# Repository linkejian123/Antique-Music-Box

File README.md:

# Antique-Music-Box

### Description
-This project was originally a senior design project in Purdue University ECE477. 
-This is a music player capable of playing mp3 on SD card or stream Bluetooth music from Android devices. The music box has digital amplifier and valve tube pre-amp. The display used 60s style VFD tube from Soviet era.
-The Microcontroller used is Microchips dsPIC33FJ256GP710A.
- !!!!  Demo Vidoe here:https://www.youtube.com/watch?v=YaUscYTW8Vs&t=1s

### Authors
-Kejian Lin
-Ran An
-Yixing Liu
-Zhiyi Xiang

### Repository Structure

-`main`,`mp3`,`sd`, `AntiqueMB.X` are the code for the PIC microcontroller for main, mp3 and sd card as it states.
- `multithread` is the experimental multithread code.
- `arduino` is the interface code for Arduino Uno.
- `CAD` is the conceptual SolidWorks model for the project.
- `OBJ477` is the PCB files in Eagle. 

### Warning
 #### High voltage
 #### Some hotfix are not documented, yet

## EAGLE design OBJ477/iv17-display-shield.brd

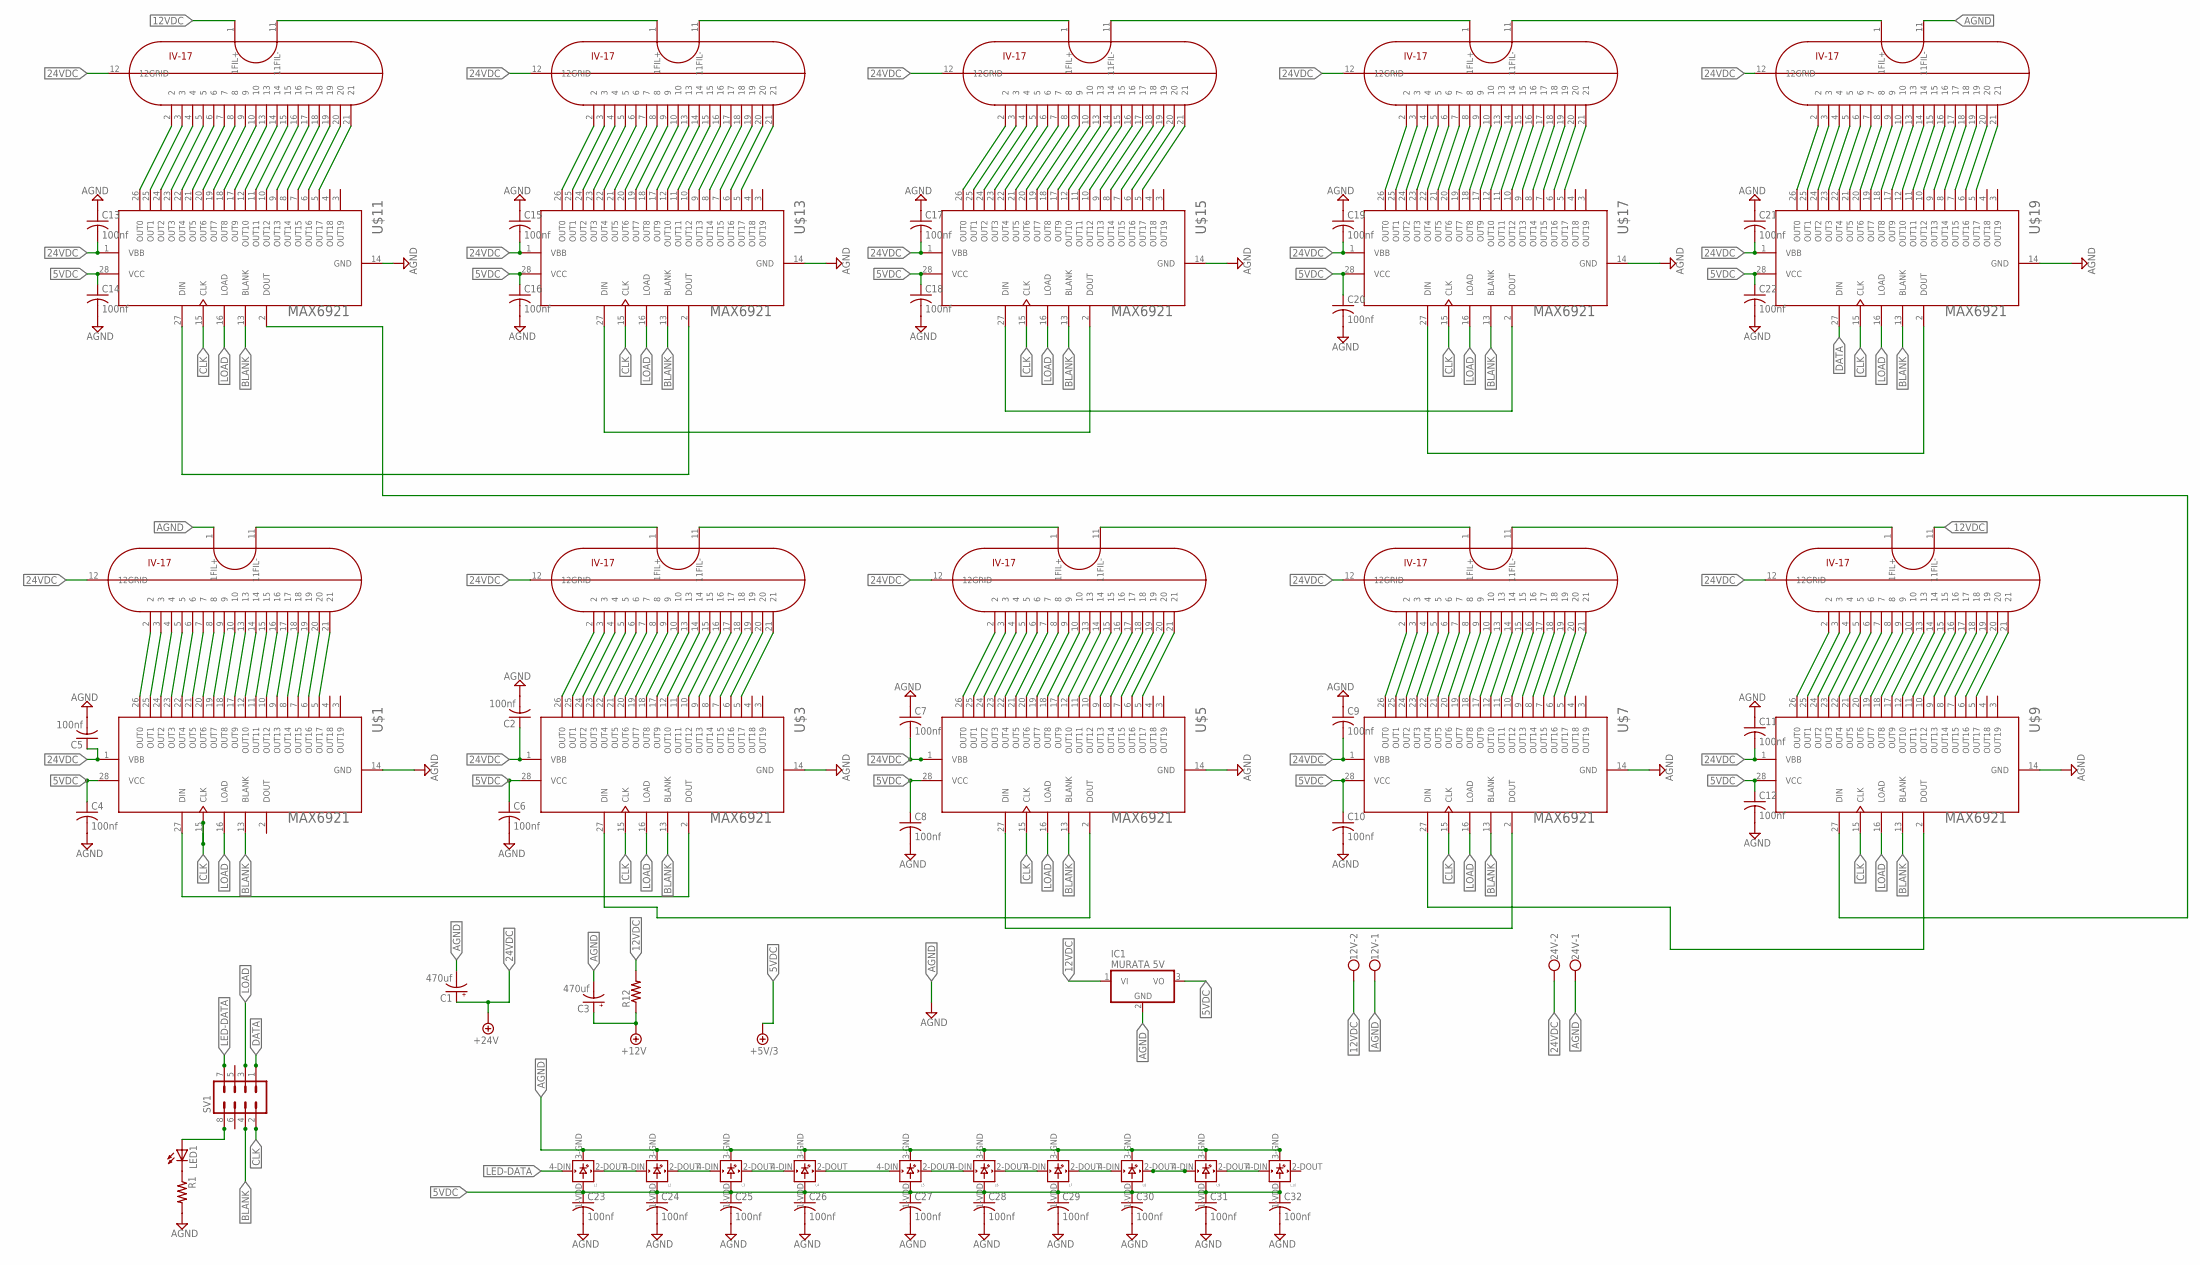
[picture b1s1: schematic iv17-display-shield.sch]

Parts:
12V, 24V: W237-102
C1, C3: 470uf; E5-10,5
C2, C4, C5, C6, C7, C8, C9, C10, C11, C12, C13, C14, C15, C16, C17, C18, C19, C20, C21, C22, C23, C24, C25, C26, C27, C28, C29, C30, C31, C32: 100nf; C1206
IC1: MURATA 5V; TO220V
L1, L2, L3, L4, L5, L6, L7, L8, L9, L10: WS2812B
LED1: LEDSMT1206; 1206
R1: R-US_R1206; R1206
R12: R-US_0207/10; 0207/10
SV1: MA04-2
U$1, U$3, U$5, U$7, U$9, U$11, U$13, U$15, U$17, U$19: MAX6921; SOIC-28W
U$2, U$4, U$6, U$8, U$10, U$12, U$14, U$16, U$18, U$20: IV17; NIXIE-22

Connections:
5VDC: C4.1, C6.1, C8.1, C10.1, C12.1, C14.1, C16.1, C18.1, C20.1, C22.1, C23.1, C24.1, C25.1, C26.1, C27.1, C28.1, C29.1, C30.1, C31.1, C32.1, IC1.3 (VO), L1.1-VDD (VDD), L2.1-VDD (VDD), L3.1-VDD (VDD), L4.1-VDD (VDD), L5.1-VDD (VDD), L6.1-VDD (VDD), L7.1-VDD (VDD), L8.1-VDD (VDD), L9.1-VDD (VDD), L10.1-VDD (VDD), U$1.28 (VCC), U$3.28 (VCC), U$5.28 (VCC), U$7.28 (VCC), U$9.28 (VCC), U$11.28 (VCC), U$13.28 (VCC), U$15.28 (VCC), U$17.28 (VCC), U$19.28 (VCC)
12VDC: 12V.2, IC1.1 (VI), R12.2, U$10.11 (11FIL-), U$12.1 (1FIL+)
24VDC: 24V.2, C1.+, C2.1, C5.1, C7.2, C9.2, C11.2, C13.2, C15.2, C17.2, C19.2, C21.2, U$1.1 (VBB), U$2.12 (12GRID), U$3.1 (VBB), U$4.12 (12GRID), U$5.1 (VBB), U$6.12 (12GRID), U$7.1 (VBB), U$8.12 (12GRID), U$9.1 (VBB), U$10.12 (12GRID), U$11.1 (VBB), U$12.12 (12GRID), U$13.1 (VBB), U$14.12 (12GRID), U$15.1 (VBB), U$16.12 (12GRID), U$17.1 (VBB), U$18.12 (12GRID), U$19.1 (VBB), U$20.12 (12GRID)
+12V: C3.+, R12.1
AGND: 12V.1, 24V.1, C1.-, C2.2, C3.-, C4.2, C5.2, C6.2, C7.1, C8.2, C9.1, C10.2, C11.1, C12.2, C13.1, C14.2, C15.1, C16.2, C17.1, C18.2, C19.1, C20.2, C21.1, C22.2, C23.2, C24.2, C25.2, C26.2, C27.2, C28.2, C29.2, C30.2, C31.2, C32.2, IC1.2 (GND), L1.3-GND (GND), L2.3-GND (GND), L3.3-GND (GND), L4.3-GND (GND), L5.3-GND (GND), L6.3-GND (GND), L7.3-GND (GND), L8.3-GND (GND), L9.3-GND (GND), L10.3-GND (GND), R1.2, U$1.14 (GND), U$2.1 (1FIL+), U$3.14 (GND), U$5.14 (GND), U$7.14 (GND), U$9.14 (GND), U$11.14 (GND), U$13.14 (GND), U$15.14 (GND), U$17.14 (GND), U$19.14 (GND), U$20.11 (11FIL-)
BLANK: SV1.4, U$1.13 (BLANK), U$3.13 (BLANK), U$5.13 (BLANK), U$7.13 (BLANK), U$9.13 (BLANK), U$11.13 (BLANK), U$13.13 (BLANK), U$15.13 (BLANK), U$17.13 (BLANK), U$19.13 (BLANK)
CLK: SV1.2, U$1.15 (CLK), U$3.15 (CLK), U$5.15 (CLK), U$7.15 (CLK), U$9.15 (CLK), U$11.15 (CLK), U$13.15 (CLK), U$15.15 (CLK), U$17.15 (CLK), U$19.15 (CLK)
DATA: SV1.1, U$19.27 (DIN)
LED-DATA: L1.4-DIN (DIN), SV1.7
LOAD: SV1.3, U$1.16 (LOAD), U$3.16 (LOAD), U$5.16 (LOAD), U$7.16 (LOAD), U$9.16 (LOAD), U$11.16 (LOAD), U$13.16 (LOAD), U$15.16 (LOAD), U$17.16 (LOAD), U$19.16 (LOAD)
unnamed: U$1.26 (OUT0), U$2.2
unnamed: U$1.25 (OUT1), U$2.3
unnamed: U$1.24 (OUT2), U$2.4
unnamed: U$1.23 (OUT3), U$2.5
unnamed: U$1.22 (OUT4), U$2.6
unnamed: U$1.21 (OUT5), U$2.7
unnamed: U$1.20 (OUT6), U$2.8
unnamed: U$1.19 (OUT7), U$2.9
unnamed: U$1.18 (OUT8), U$2.10
unnamed: U$1.17 (OUT9), U$2.13
unnamed: U$1.12 (OUT10), U$2.14
unnamed: U$1.11 (OUT11), U$2.15
unnamed: U$1.10 (OUT12), U$2.16
unnamed: U$1.9 (OUT13), U$2.17
unnamed: U$1.8 (OUT14), U$2.18
unnamed: U$1.7 (OUT15), U$2.19
unnamed: U$1.6 (OUT16), U$2.20
unnamed: U$1.5 (OUT17), U$2.21
unnamed: U$3.26 (OUT0), U$4.2
unnamed: U$3.25 (OUT1), U$4.3
unnamed: U$3.24 (OUT2), U$4.4
unnamed: U$3.23 (OUT3), U$4.5
unnamed: U$17.27 (DIN), U$19.2 (DOUT)
unnamed: U$3.22 (OUT4), U$4.6
unnamed: U$3.21 (OUT5), U$4.7
unnamed: U$3.20 (OUT6), U$4.8
unnamed: U$3.19 (OUT7), U$4.9
unnamed: U$3.18 (OUT8), U$4.10
unnamed: U$3.17 (OUT9), U$4.13
unnamed: U$3.12 (OUT10), U$4.14
unnamed: U$3.11 (OUT11), U$4.15
unnamed: U$3.10 (OUT12), U$4.16
unnamed: U$3.9 (OUT13), U$4.17
unnamed: U$3.8 (OUT14), U$4.18
unnamed: U$3.7 (OUT15), U$4.19
unnamed: U$3.6 (OUT16), U$4.20
unnamed: U$3.5 (OUT17), U$4.21
unnamed: U$5.26 (OUT0), U$6.2
unnamed: U$5.25 (OUT1), U$6.3
unnamed: U$5.24 (OUT2), U$6.4
unnamed: U$15.27 (DIN), U$17.2 (DOUT)
unnamed: U$5.23 (OUT3), U$6.5
unnamed: U$5.22 (OUT4), U$6.6
unnamed: U$5.21 (OUT5), U$6.7
unnamed: U$5.20 (OUT6), U$6.8
unnamed: U$5.19 (OUT7), U$6.9
unnamed: U$5.18 (OUT8), U$6.10
unnamed: U$5.17 (OUT9), U$6.13
unnamed: U$5.12 (OUT10), U$6.14
unnamed: U$5.11 (OUT11), U$6.15
unnamed: U$5.10 (OUT12), U$6.16
unnamed: U$5.9 (OUT13), U$6.17
unnamed: U$5.8 (OUT14), U$6.18
unnamed: U$5.7 (OUT15), U$6.19
unnamed: U$5.6 (OUT16), U$6.20
unnamed: U$5.5 (OUT17), U$6.21
unnamed: U$7.26 (OUT0), U$8.2
unnamed: U$7.25 (OUT1), U$8.3
unnamed: U$7.24 (OUT2), U$8.4
unnamed: U$7.23 (OUT3), U$8.5
unnamed: U$7.22 (OUT4), U$8.6
unnamed: U$7.21 (OUT5), U$8.7
unnamed: U$11.27 (DIN), U$13.2 (DOUT)
unnamed: U$7.20 (OUT6), U$8.8
unnamed: U$7.19 (OUT7), U$8.9
unnamed: U$7.18 (OUT8), U$8.10
unnamed: U$7.17 (OUT9), U$8.13
unnamed: U$7.12 (OUT10), U$8.14
unnamed: U$7.11 (OUT11), U$8.15
unnamed: U$7.10 (OUT12), U$8.16
unnamed: U$7.9 (OUT13), U$8.17
unnamed: U$7.8 (OUT14), U$8.18
unnamed: U$7.7 (OUT15), U$8.19
unnamed: U$7.6 (OUT16), U$8.20
unnamed: U$7.5 (OUT17), U$8.21
unnamed: U$9.26 (OUT0), U$10.2
unnamed: U$9.25 (OUT1), U$10.3
unnamed: U$9.24 (OUT2), U$10.4
unnamed: U$9.23 (OUT3), U$10.5
unnamed: U$9.22 (OUT4), U$10.6
unnamed: U$9.21 (OUT5), U$10.7
unnamed: U$9.20 (OUT6), U$10.8
unnamed: U$9.19 (OUT7), U$10.9
unnamed: U$9.18 (OUT8), U$10.10
unnamed: U$9.27 (DIN), U$11.2 (DOUT)
unnamed: U$9.17 (OUT9), U$10.13
unnamed: U$9.12 (OUT10), U$10.14
unnamed: U$9.11 (OUT11), U$10.15
unnamed: U$9.10 (OUT12), U$10.16
unnamed: U$9.9 (OUT13), U$10.17
unnamed: U$9.8 (OUT14), U$10.18
unnamed: U$9.7 (OUT15), U$10.19
unnamed: U$9.6 (OUT16), U$10.20
unnamed: U$9.5 (OUT17), U$10.21
unnamed: U$11.26 (OUT0), U$12.2
unnamed: U$11.25 (OUT1), U$12.3
unnamed: U$11.24 (OUT2), U$12.4
unnamed: U$11.23 (OUT3), U$12.5
unnamed: U$11.22 (OUT4), U$12.6
unnamed: U$11.21 (OUT5), U$12.7
unnamed: U$11.20 (OUT6), U$12.8
unnamed: U$11.19 (OUT7), U$12.9
unnamed: U$11.18 (OUT8), U$12.10
unnamed: U$11.17 (OUT9), U$12.13
unnamed: U$11.12 (OUT10), U$12.14
unnamed: U$11.11 (OUT11), U$12.15
unnamed: U$7.27 (DIN), U$9.2 (DOUT)
unnamed: U$11.10 (OUT12), U$12.16
unnamed: L1.2-DOUT (DOUT), L2.4-DIN (DIN)
unnamed: L2.2-DOUT (DOUT), L3.4-DIN (DIN)
unnamed: U$8.11 (11FIL-), U$10.1 (1FIL+)
unnamed: U$6.11 (11FIL-), U$8.1 (1FIL+)
unnamed: U$4.11 (11FIL-), U$6.1 (1FIL+)
unnamed: U$2.11 (11FIL-), U$4.1 (1FIL+)
unnamed: U$11.9 (OUT13), U$12.17
unnamed: U$11.8 (OUT14), U$12.18
unnamed: U$11.7 (OUT15), U$12.19
unnamed: U$11.6 (OUT16), U$12.20
unnamed: U$11.5 (OUT17), U$12.21
unnamed: U$13.26 (OUT0), U$14.2
unnamed: U$13.25 (OUT1), U$14.3
unnamed: U$13.24 (OUT2), U$14.4
unnamed: U$13.23 (OUT3), U$14.5
unnamed: U$13.22 (OUT4), U$14.6
unnamed: U$13.21 (OUT5), U$14.7
unnamed: U$13.20 (OUT6), U$14.8
unnamed: U$13.19 (OUT7), U$14.9
unnamed: U$13.18 (OUT8), U$14.10
unnamed: U$13.17 (OUT9), U$14.13
unnamed: U$13.12 (OUT10), U$14.14
unnamed: U$13.11 (OUT11), U$14.15
unnamed: U$13.10 (OUT12), U$14.16
unnamed: U$5.27 (DIN), U$7.2 (DOUT)
unnamed: U$13.9 (OUT13), U$14.17
unnamed: L3.2-DOUT (DOUT), L4.4-DIN (DIN)
unnamed: U$13.8 (OUT14), U$14.18
unnamed: U$13.7 (OUT15), U$14.19
unnamed: U$13.6 (OUT16), U$14.20
unnamed: U$13.5 (OUT17), U$14.21
unnamed: U$15.26 (OUT0), U$16.2
unnamed: U$15.25 (OUT1), U$16.3
unnamed: U$15.24 (OUT2), U$16.4
unnamed: U$15.23 (OUT3), U$16.5
unnamed: U$15.22 (OUT4), U$16.6
unnamed: U$15.21 (OUT5), U$16.7
unnamed: U$15.20 (OUT6), U$16.8
unnamed: U$15.19 (OUT7), U$16.9
unnamed: U$15.18 (OUT8), U$16.10
unnamed: U$15.17 (OUT9), U$16.13
unnamed: U$15.12 (OUT10), U$16.14
unnamed: U$15.11 (OUT11), U$16.15
unnamed: U$15.10 (OUT12), U$16.16
unnamed: U$15.9 (OUT13), U$16.17
unnamed: U$15.8 (OUT14), U$16.18
unnamed: U$3.27 (DIN), U$5.2 (DOUT)
unnamed: U$15.7 (OUT15), U$16.19
unnamed: L4.2-DOUT (DOUT), L5.4-DIN (DIN)
unnamed: L5.2-DOUT (DOUT), L6.4-DIN (DIN)
unnamed: U$15.6 (OUT16), U$16.20
unnamed: U$15.5 (OUT17), U$16.21
unnamed: U$17.26 (OUT0), U$18.2
unnamed: U$17.25 (OUT1), U$18.3
unnamed: U$17.24 (OUT2), U$18.4
unnamed: U$17.23 (OUT3), U$18.5
unnamed: U$17.22 (OUT4), U$18.6
unnamed: U$17.21 (OUT5), U$18.7
unnamed: U$17.20 (OUT6), U$18.8
unnamed: U$17.19 (OUT7), U$18.9
unnamed: U$17.18 (OUT8), U$18.10
unnamed: U$17.17 (OUT9), U$18.13
unnamed: U$17.12 (OUT10), U$18.14
unnamed: U$17.11 (OUT11), U$18.15
unnamed: U$17.10 (OUT12), U$18.16
unnamed: U$17.9 (OUT13), U$18.17
unnamed: U$17.8 (OUT14), U$18.18
unnamed: U$17.7 (OUT15), U$18.19
unnamed: U$13.27 (DIN), U$15.2 (DOUT)
unnamed: U$17.6 (OUT16), U$18.20
unnamed: L6.2-DOUT (DOUT), L7.4-DIN (DIN)
unnamed: L7.2-DOUT (DOUT), L8.4-DIN (DIN)
unnamed: U$17.5 (OUT17), U$18.21
unnamed: U$19.26 (OUT0), U$20.2
unnamed: U$19.25 (OUT1), U$20.3
unnamed: U$19.24 (OUT2), U$20.4
unnamed: U$19.23 (OUT3), U$20.5
unnamed: U$19.22 (OUT4), U$20.6
unnamed: U$19.21 (OUT5), U$20.7
unnamed: U$19.20 (OUT6), U$20.8
unnamed: U$19.19 (OUT7), U$20.9
unnamed: U$19.18 (OUT8), U$20.10
unnamed: U$19.17 (OUT9), U$20.13
unnamed: U$19.12 (OUT10), U$20.14
unnamed: U$19.11 (OUT11), U$20.15
unnamed: U$19.10 (OUT12), U$20.16
unnamed: U$19.9 (OUT13), U$20.17
unnamed: U$19.8 (OUT14), U$20.18
unnamed: U$19.7 (OUT15), U$20.19
unnamed: U$19.6 (OUT16), U$20.20
unnamed: U$1.27 (DIN), U$3.2 (DOUT)
unnamed: U$19.5 (OUT17), U$20.21
unnamed: L8.2-DOUT (DOUT), L9.4-DIN (DIN)
unnamed: L9.2-DOUT (DOUT), L10.4-DIN (DIN)
unnamed: LED1.C, R1.1
unnamed: LED1.A, SV1.8
unnamed: U$18.11 (11FIL-), U$20.1 (1FIL+)
unnamed: U$16.11 (11FIL-), U$18.1 (1FIL+)
unnamed: U$14.11 (11FIL-), U$16.1 (1FIL+)
unnamed: U$12.11 (11FIL-), U$14.1 (1FIL+)

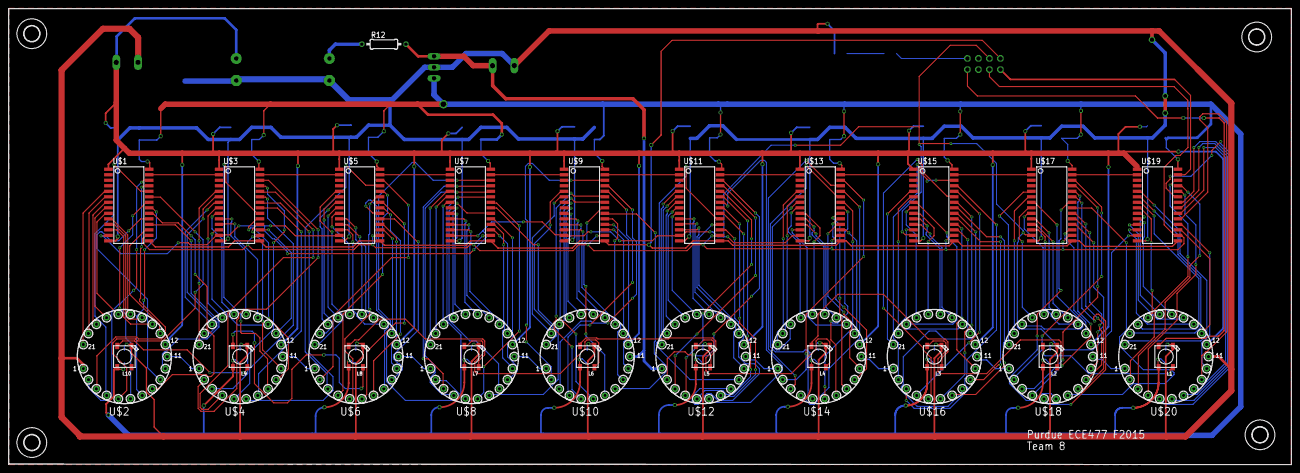
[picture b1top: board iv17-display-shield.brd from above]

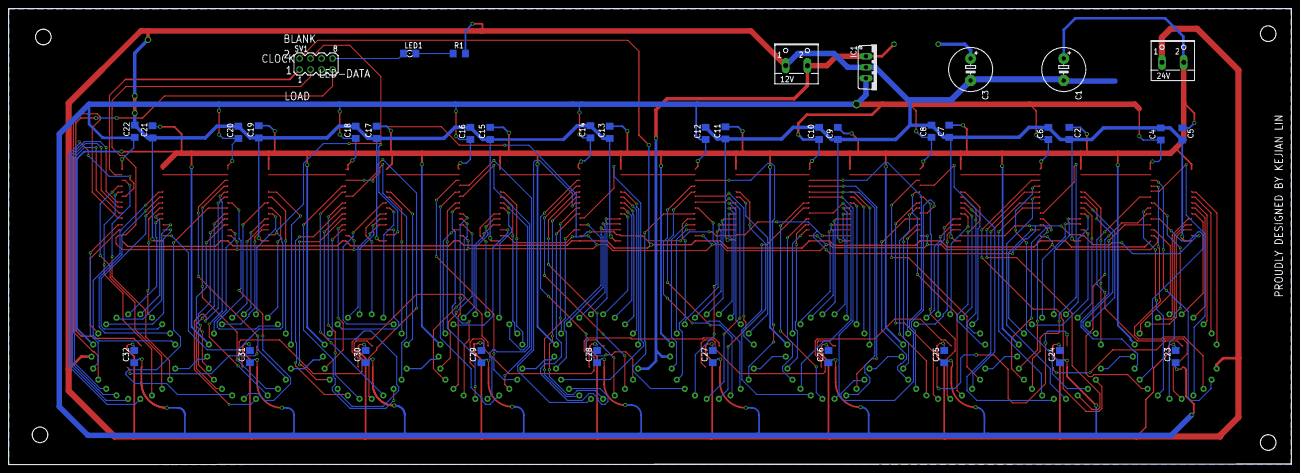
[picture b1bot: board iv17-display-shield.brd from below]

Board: 2 copper layers, 295.6 x 105.1 mm, 73 parts (38 on the bottom side), 218 nets.

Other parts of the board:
U$21, U$22, U$23, U$24: 3,6

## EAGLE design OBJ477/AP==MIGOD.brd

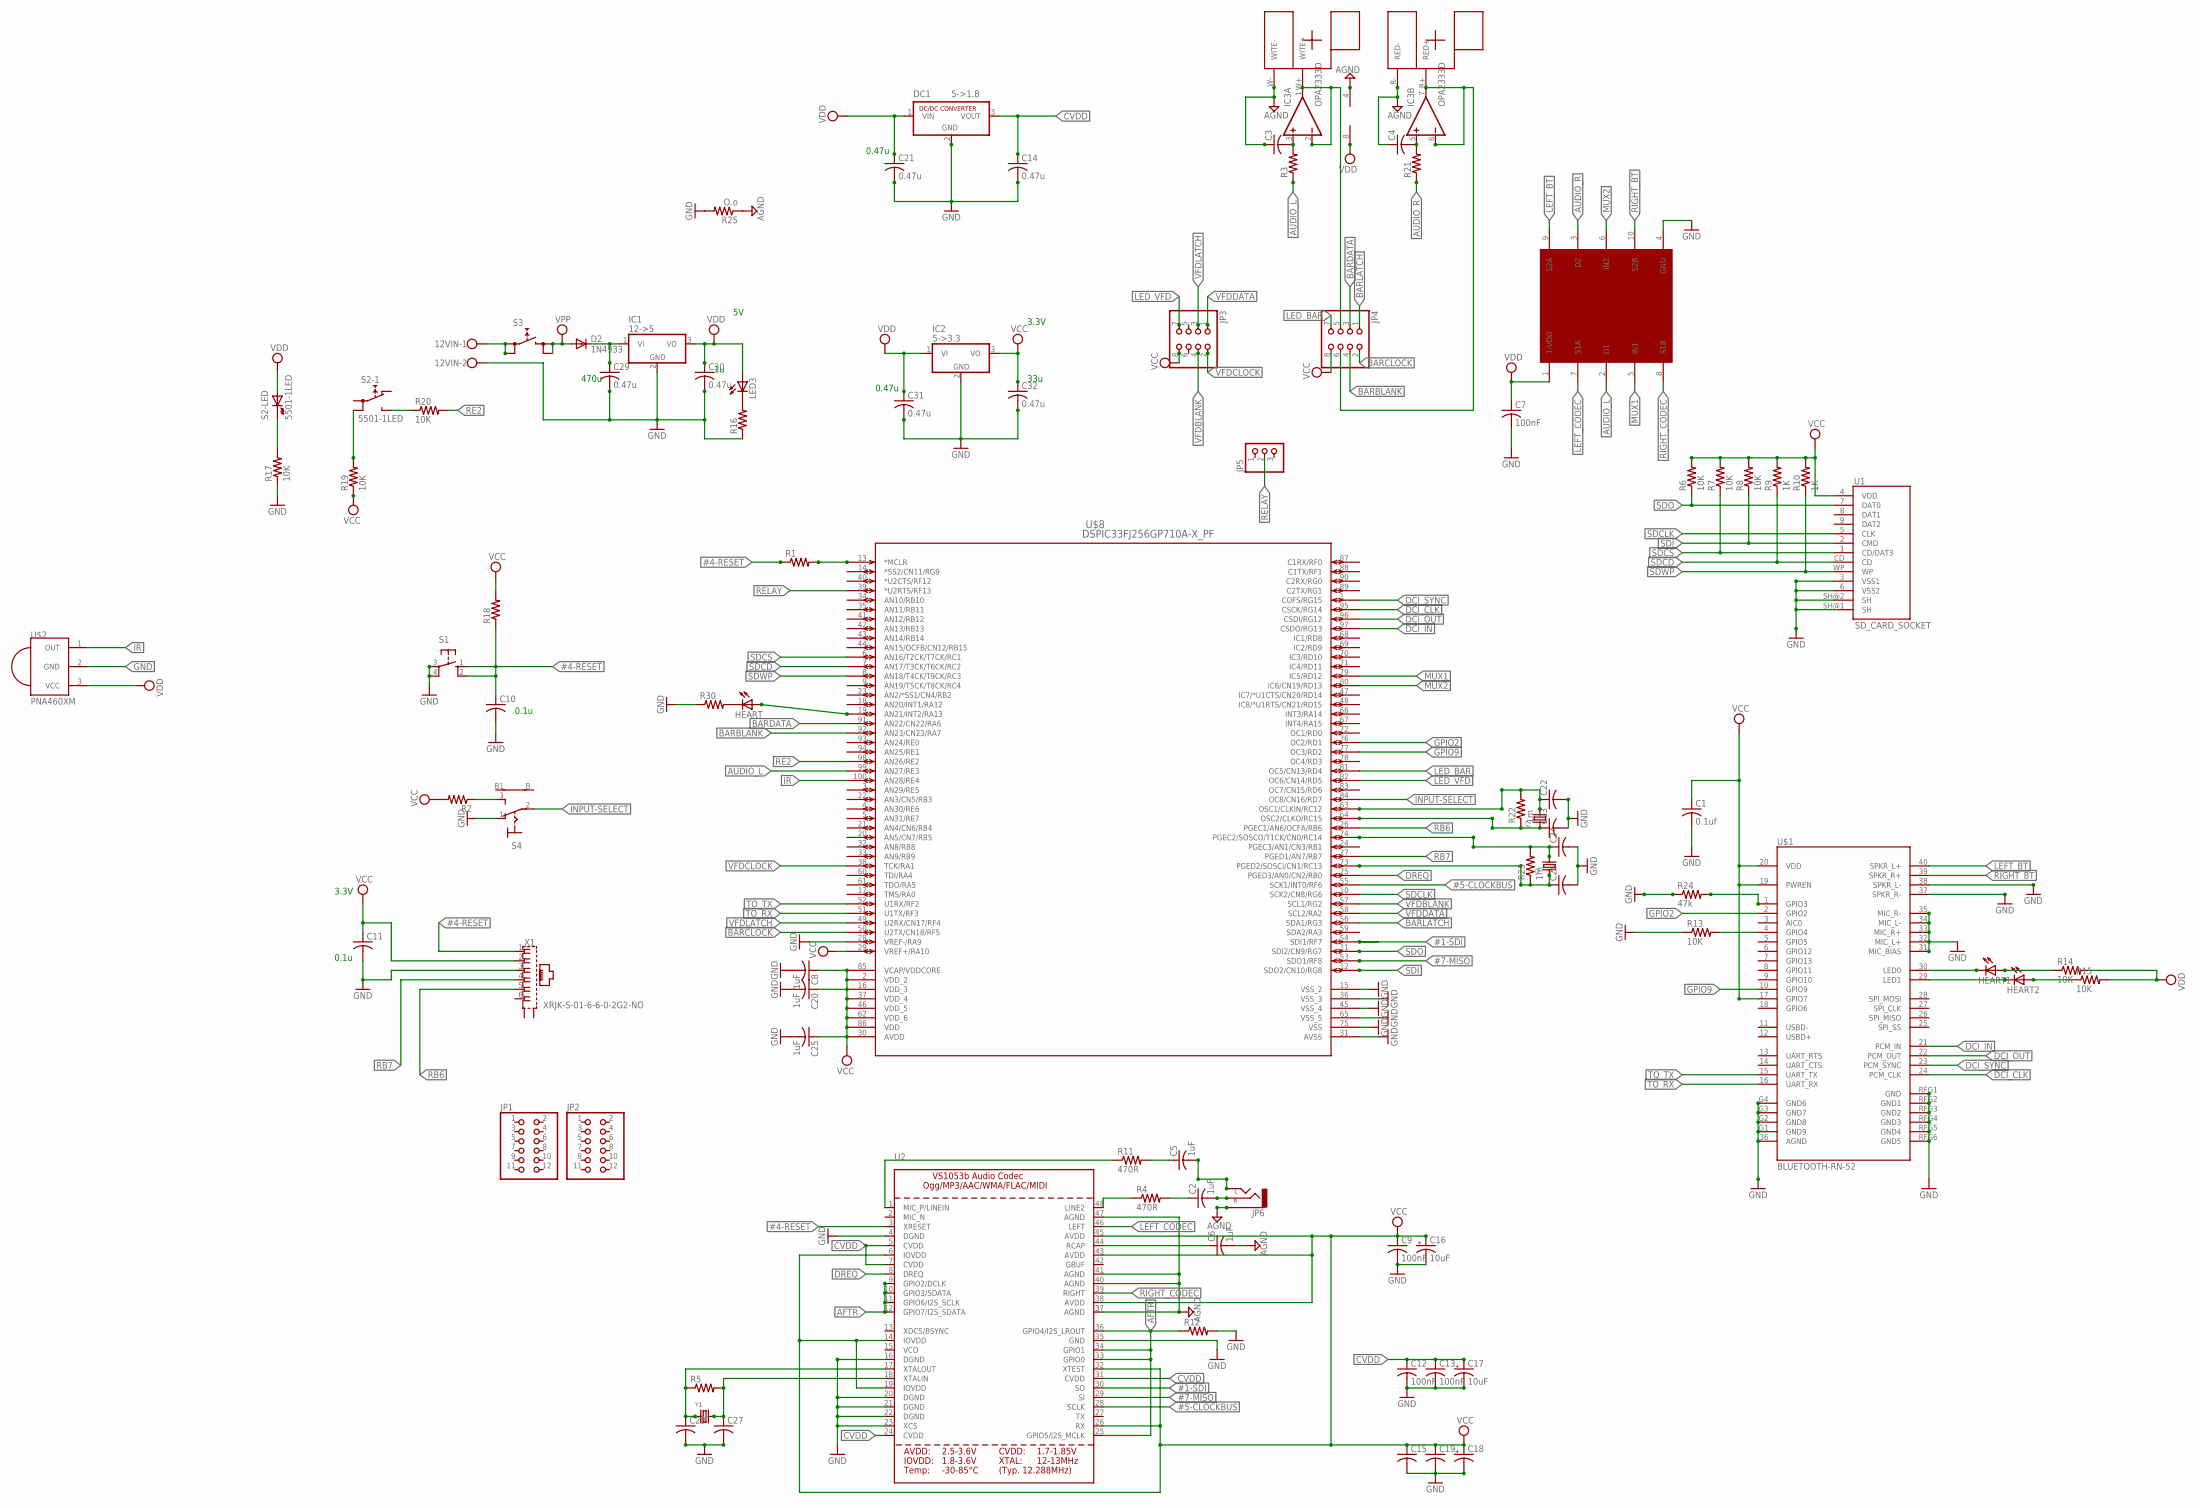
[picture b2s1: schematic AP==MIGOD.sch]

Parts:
12VIN: W237-102
C1: 0.1uf; C1206
C2, C5, C6, C8, C20, C25: 1uF; C1206
C3, C4: C-US050-030X075; C050-030X075
C7, C9, C12, C13: 100nF; C1206
C10, C11, C15, C19, C22, C23, C24, C26, C27, C28: C-USC1206; C1206
C14, C21, C29, C30, C31, C32: 0.47u; C1206
C16, C17: 10uF; E5-8,5
C18: CPOL-USE5-8.5; E5-8,5
D2: 1N4933; DO41-10
DC1: 5->1.8; SIP3
HEART, HEART1, HEART2: LEDSMT1206; 1206
IC1: 12->5; TO220V
IC2: 5->3.3; TO220V
IC3: OPA2333D; SO08
JP1, JP2: PINHD-2X6; 2X06
JP3, JP4: PINHD-2X4; 2X04
JP5: PINHD-1X3; 1X03
JP6: AUDIO-JACKPTH; AUDIO-JACK
LED3: LEDSMT1206; 1206
R1, R2, R5, R12, R16, R18, R30: R-US_R1206; R1206
R3, R21: R-US_0207/10; 0207/10
R4, R11: 470R; R1206
R6, R7, R8, R13, R14, R15, R17, R19, R20: 10K; R1206
R9, R10: 1K; R1206
R22, R23: 1m; R1206
R24: 47k; R1206
R25: O.o; R1206
S1: 10-XX; B3F-10XX
S2: 5501-1LED
S3: REKN
S4: 9070-1W
U1: SD_CARD_SOCKET; SD_1:1
U2: VS1053B; LQFP48
U$1: BLUETOOTH-RN-52; RN-52
U$2: PNA460XM
U$8: DSPIC33FJ256GP710A-X_PF; TQFP100_14X14MC
U$13: RCANEW; RCA
U$15: ADG884; MSOP10
X1: XRJK-S-01-6-6-0-2G2-NO
Y1, Y2, Y3: CRYSTALTHIN; CRYSTAL_3.2X2.5

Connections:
#1-SDI: U2.30 (SO), U$8.54 (SDI1/RF7)
#4-RESET: C10.1, R1.1, R18.1, S1.1 (S), S1.2 (S1), U2.3 (XRESET), X1.1
#5-CLOCKBUS: U2.28 (SCLK), U$8.55 (SCK1/INT0/RF6)
#7-MISO: U2.29 (SI), U$8.53 (SDO1/RF8)
AFTR: R12.1, U2.9 (GPIO2/DCLK), U2.10 (GPIO3/SDATA), U2.11 (GPIO6/I2S_SCLK), U2.12 (GPIO7/I2S_SDATA), U2.25 (GPIO5/I2S_MCLK), U2.33 (GPIO0), U2.34 (GPIO1), U2.36 (GPIO4/I2S_LROUT)
AGND: C3.1, C4.1, C6.2, IC3.4 (V-), JP6.SLEEVE, R25.1, U2.37 (AGND), U2.40 (AGND), U2.41 (AGND), U2.47 (AGND), U$13.R- (RED-), U$13.W- (WITE-)
AUDIO_L: R3.1, U$8.99 (AN27/RE3), U$15.2 (D1)
AUDIO_R: R21.1, U$15.3 (D2)
BARBLANK: JP4.4, U$8.92 (AN23/CN23/RA7)
BARCLOCK: JP4.2, U$8.50 (U2TX/CN18/RF5)
BARDATA: JP4.3, U$8.91 (AN22/CN22/RA6)
BARLATCH: JP4.1, U$8.56 (SDA1/RG3)
CVDD: C12.1, C13.1, C14.1, C17.+, DC1.3 (VOUT), U2.5 (CVDD), U2.7 (CVDD), U2.24 (CVDD), U2.31 (CVDD)
DCI_CLK: U$1.24 (PCM_CLK), U$8.95 (CSCK/RG14)
DCI_IN: U$1.21 (PCM_IN), U$8.97 (CSDO/RG13)
DCI_OUT: U$1.22 (PCM_OUT), U$8.96 (CSDI/RG12)
DCI_SYNC: U$1.23 (PCM_SYNC), U$8.1 (COFS/RG15)
DREQ: U2.8 (DREQ), U$8.25 (PGED3/AN0/CN2/RB0)
GND: 12VIN.2, C1.2, C7.2, C8.2, C9.2, C10.2, C11.2, C12.2, C13.2, C14.2, C15.2, C16.-, C17.-, C18.-, C19.2, C20.2, C21.2, C22.2, C23.2, C24.2, C25.2, C26.2, C27.2, C28.2, C29.2, C30.2, C31.2, C32.2, DC1.2 (GND), IC1.2 (GND), IC2.2 (GND), R12.2, R13.1, R16.1, R17.1, R24.1, R25.2, R30.1, S1.3, S1.4 (P1), S4.1 (O), U1.3 (VSS1), U1.6 (VSS2), U1.SH@1 (SH), U1.SH@2 (SH), U2.4 (DGND), U2.16 (DGND), U2.20 (DGND), U2.21 (DGND), U2.22 (DGND), U2.23 (XCS), U2.35 (GND), U$1.31 (MIC_BIAS), U$1.32 (MIC_L+), U$1.33 (MIC_R+), U$1.34 (MIC_L-), U$1.35 (MIC_R-), U$1.36 (AGND), U$1.37 (SPKR_R-), U$1.38 (SPKR_L-), U$1.G1 (GND9), U$1.G2 (GND8), U$1.G3 (GND7), U$1.G4 (GND6), U$1.RFG1 (GND), U$1.RFG2 (GND1), U$1.RFG3 (GND2), U$1.RFG4 (GND3), U$1.RFG5 (GND4), U$1.RFG6 (GND5), U$2.2 (GND), U$8.15 (VSS_2), U$8.28 (VREF-/RA9), U$8.31 (AVSS), U$8.36 (VSS_3), U$8.45 (VSS_4), U$8.65 (VSS_5), U$8.75 (VSS), U$15.4 (GND), X1.3
GPIO2: U$1.2 (GPIO2), U$8.76 (OC2/RD1)
GPIO9: U$1.10 (GPIO9), U$8.77 (OC3/RD2)
INPUT-SELECT: S4.2, U$8.84 (OC8/CN16/RD7)
IR: U$2.1 (OUT), U$8.100 (AN28/RE4)
LED_BAR: JP4.7, U$8.81 (OC5/CN13/RD4)
LED_VFD: JP3.7, U$8.82 (OC6/CN14/RD5)
LEFT_BT: U$1.40 (SPKR_L+), U$15.9 (S2A)
LEFT_CODEC: U2.46 (LEFT), U$15.7 (S1A)
MUX1: U$8.79 (IC5/RD12), U$15.5 (IN1)
MUX2: U$8.80 (IC6/CN19/RD13), U$15.6 (IN2)
unnamed: C2.2, JP6.RING (RIGHT)
unnamed: R1.2, U$8.13 (*MCLR)
unnamed: LED3.C, R16.2
unnamed: C6.1, U2.44 (RCAP)
unnamed: R19.2, S2.1B
unnamed: C28.1, R5.1, U2.17 (XTALOUT), Y1.1
unnamed: C27.1, R5.2, U2.18 (XTALIN), Y1.2
unnamed: C2.1, R4.2
unnamed: R4.1, U2.48 (LINE2)
unnamed: C5.2, JP6.TIP (LEFT)
unnamed: C5.1, R11.2
unnamed: R11.1, U2.1 (MIC_P/LINEIN)
unnamed: C24.1, R23.2, U$8.74 (PGEC2/SOSCO/T1CK/CN0/RC14), Y3.2
unnamed: R13.2, U$1.4 (GPIO4)
unnamed: C29.1, D2.C, IC1.1 (VI)
unnamed: HEART1.C, U$1.30 (LED0)
unnamed: HEART2.C, U$1.29 (LED1)
unnamed: HEART1.A, R14.1
unnamed: HEART2.A, R15.1
unnamed: C22.1, R22.2, U$8.63 (OSC1/CLKIN/RC12), Y2.2
unnamed: IC3.1 (OUT), IC3.2 (-IN), JP4.5, U$13.W+ (WITE+)
unnamed: IC3.6 (-IN), IC3.7 (OUT), JP4.6, U$13.R+ (RED+)
unnamed: C3.2, IC3.3 (+IN), R3.2
unnamed: R17.2, S2.- (K)
unnamed: R20.1, S2.NO
unnamed: 12VIN.1, S3.0A (0), S3.0B (0)
unnamed: C4.2, IC3.5 (+IN), R21.2
unnamed: R2.1, S4.3 (S)
unnamed: R24.2, U$1.1 (GPIO3)
unnamed: C23.1, R22.1, U$8.64 (OSC2/CLKO/RC15), Y2.1
unnamed: C26.1, R23.1, U$8.73 (PGED2/SOSCI/CN1/RC13), Y3.1
unnamed: HEART.A, U$8.19 (AN21/INT2/RA13)
unnamed: HEART.C, R30.2
RB6: U$8.26 (PGEC1/AN6/OCFA/RB6), X1.5
RB7: U$8.27 (PGED1/AN7/RB7), X1.4
RE2: R20.2, U$8.98 (AN26/RE2)
RELAY: JP5.2, U$8.39 (*U2RTS/RF13)
RIGHT_BT: U$1.39 (SPKR_R+), U$15.10 (S2B)
RIGHT_CODEC: U2.39 (RIGHT), U$15.8 (S1B)
SDCD: R9.1, U1.CD, U$8.7 (AN17/T3CK/T6CK/RC2)
SDCLK: U1.5 (CLK), U$8.10 (SCK2/CN8/RG6)
SDCS: R7.1, U1.1 (CD/DAT3), U$8.6 (AN16/T2CK/T7CK/RC1)
SDI: R8.1, U1.2 (CMD), U$8.12 (SDO2/CN10/RG8)
SDO: R6.1, U1.7 (DAT0), U$8.11 (SDI2/CN9/RG7)
SDWP: R10.1, U1.WP, U$8.8 (AN18/T4CK/T9CK/RC3)
TO_RX: U$1.16 (UART_RX), U$8.51 (U1TX/RF3)
TO_TX: U$1.15 (UART_TX), U$8.52 (U1RX/RF2)
VCC: C1.1, C8.1, C9.1, C11.1, C15.1, C16.+, C18.+, C19.1, C20.1, C25.1, C32.1, IC2.3 (VO), JP3.8, JP4.8, R2.2, R6.2, R7.2, R8.2, R9.2, R10.2, R18.2, R19.1, U1.4 (VDD), U2.6 (IOVDD), U2.14 (IOVDD), U2.19 (IOVDD), U2.26 (RX), U2.32 (XTEST), U2.38 (AVDD), U2.43 (AVDD), U2.45 (AVDD), U$1.17 (GPIO7), U$1.19 (PWREN), U$1.20 (VDD), U$8.2 (VDD_2), U$8.16 (VDD_3), U$8.29 (VREF+/RA10), U$8.30 (AVDD), U$8.37 (VDD_4), U$8.46 (VDD_5), U$8.62 (VDD_6), U$8.85 (VCAP/VDDCORE), U$8.86 (VDD), X1.2
VDD: C7.1, C21.1, C30.1, C31.1, DC1.1 (VIN), IC1.3 (VO), IC2.1 (VI), IC3.8 (V+), LED3.A, R14.2, R15.2, S2.+ (A), U$2.3 (VCC), U$15.1 (1-VDD)
VFDBLANK: JP3.4, U$8.57 (SCL1/RG2)
VFDCLOCK: JP3.2, U$8.38 (TCK/RA1)
VFDDATA: JP3.1, U$8.58 (SCL2/RA2)
VFDLATCH: JP3.3, U$8.49 (U2RX/CN17/RF4)
VPP: D2.A, S3.1A (1), S3.1B (1)

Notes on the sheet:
0.1u
3.3V
470u
0.47u
33u

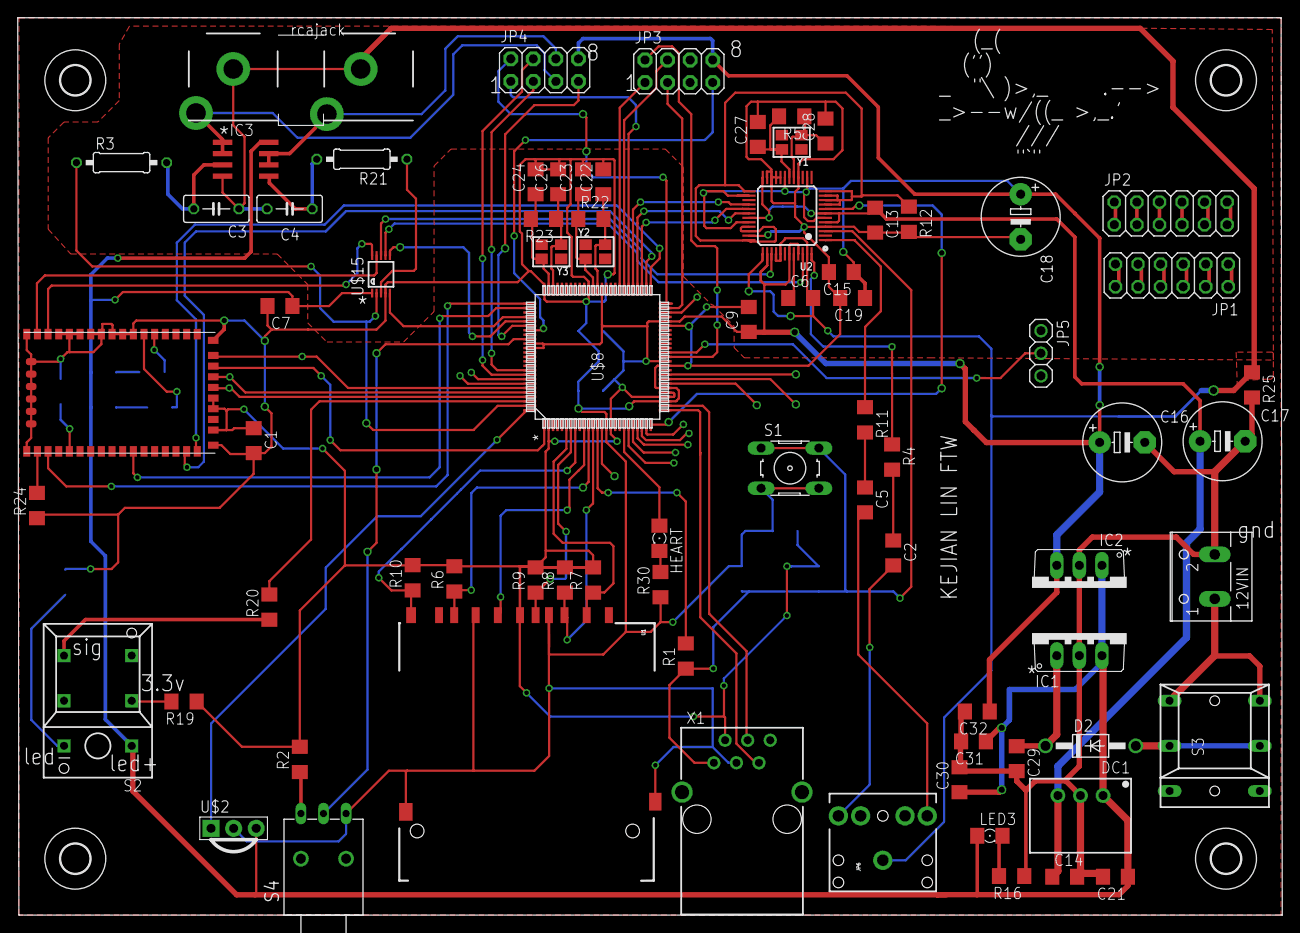
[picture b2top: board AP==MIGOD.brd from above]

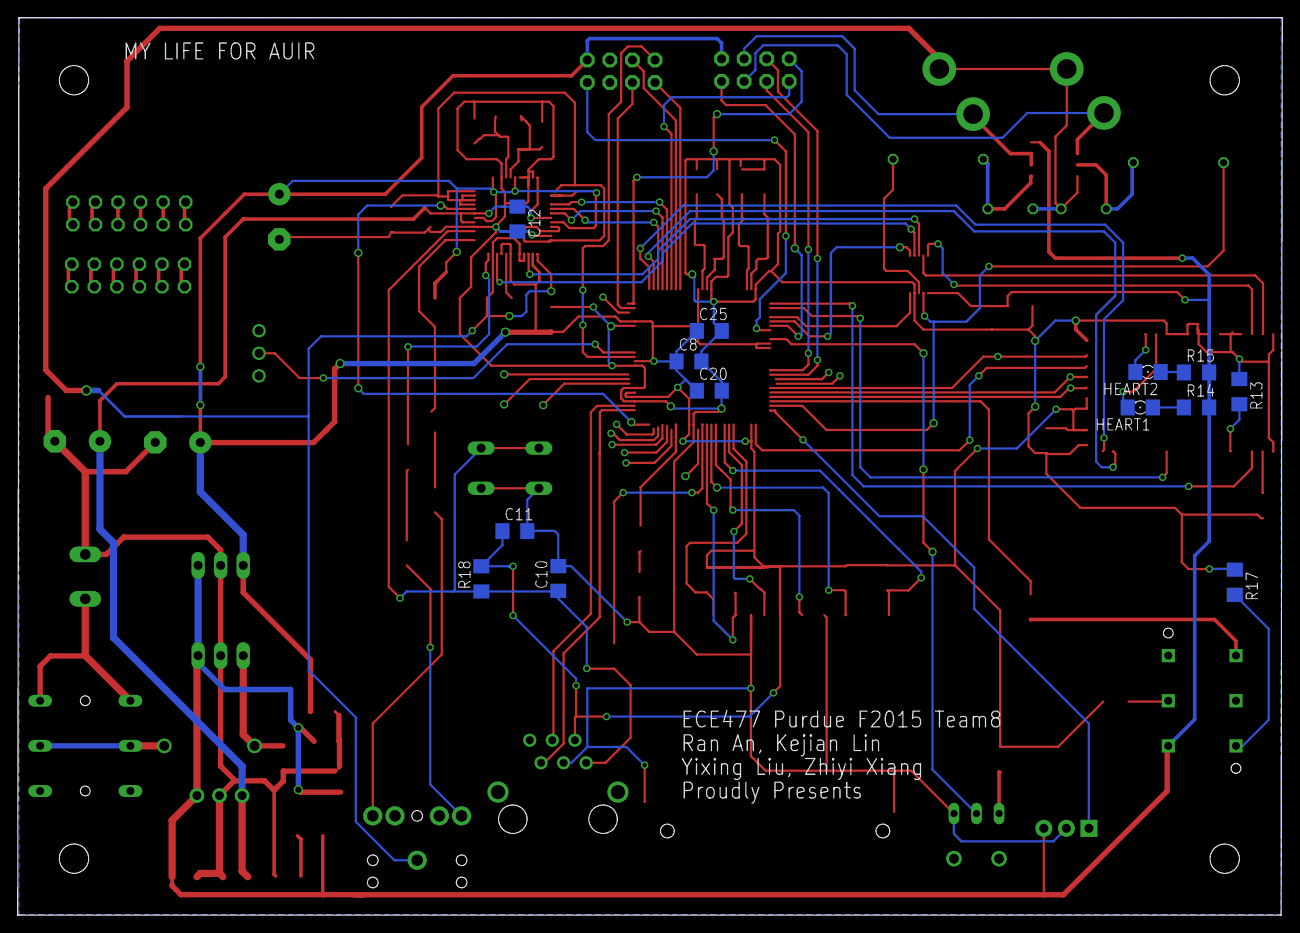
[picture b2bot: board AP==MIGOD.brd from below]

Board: 2 copper layers, 142.3 x 101.0 mm, 93 parts (13 on the bottom side), 83 nets.

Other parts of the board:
U$9, U$10, U$11, U$12: 3,3

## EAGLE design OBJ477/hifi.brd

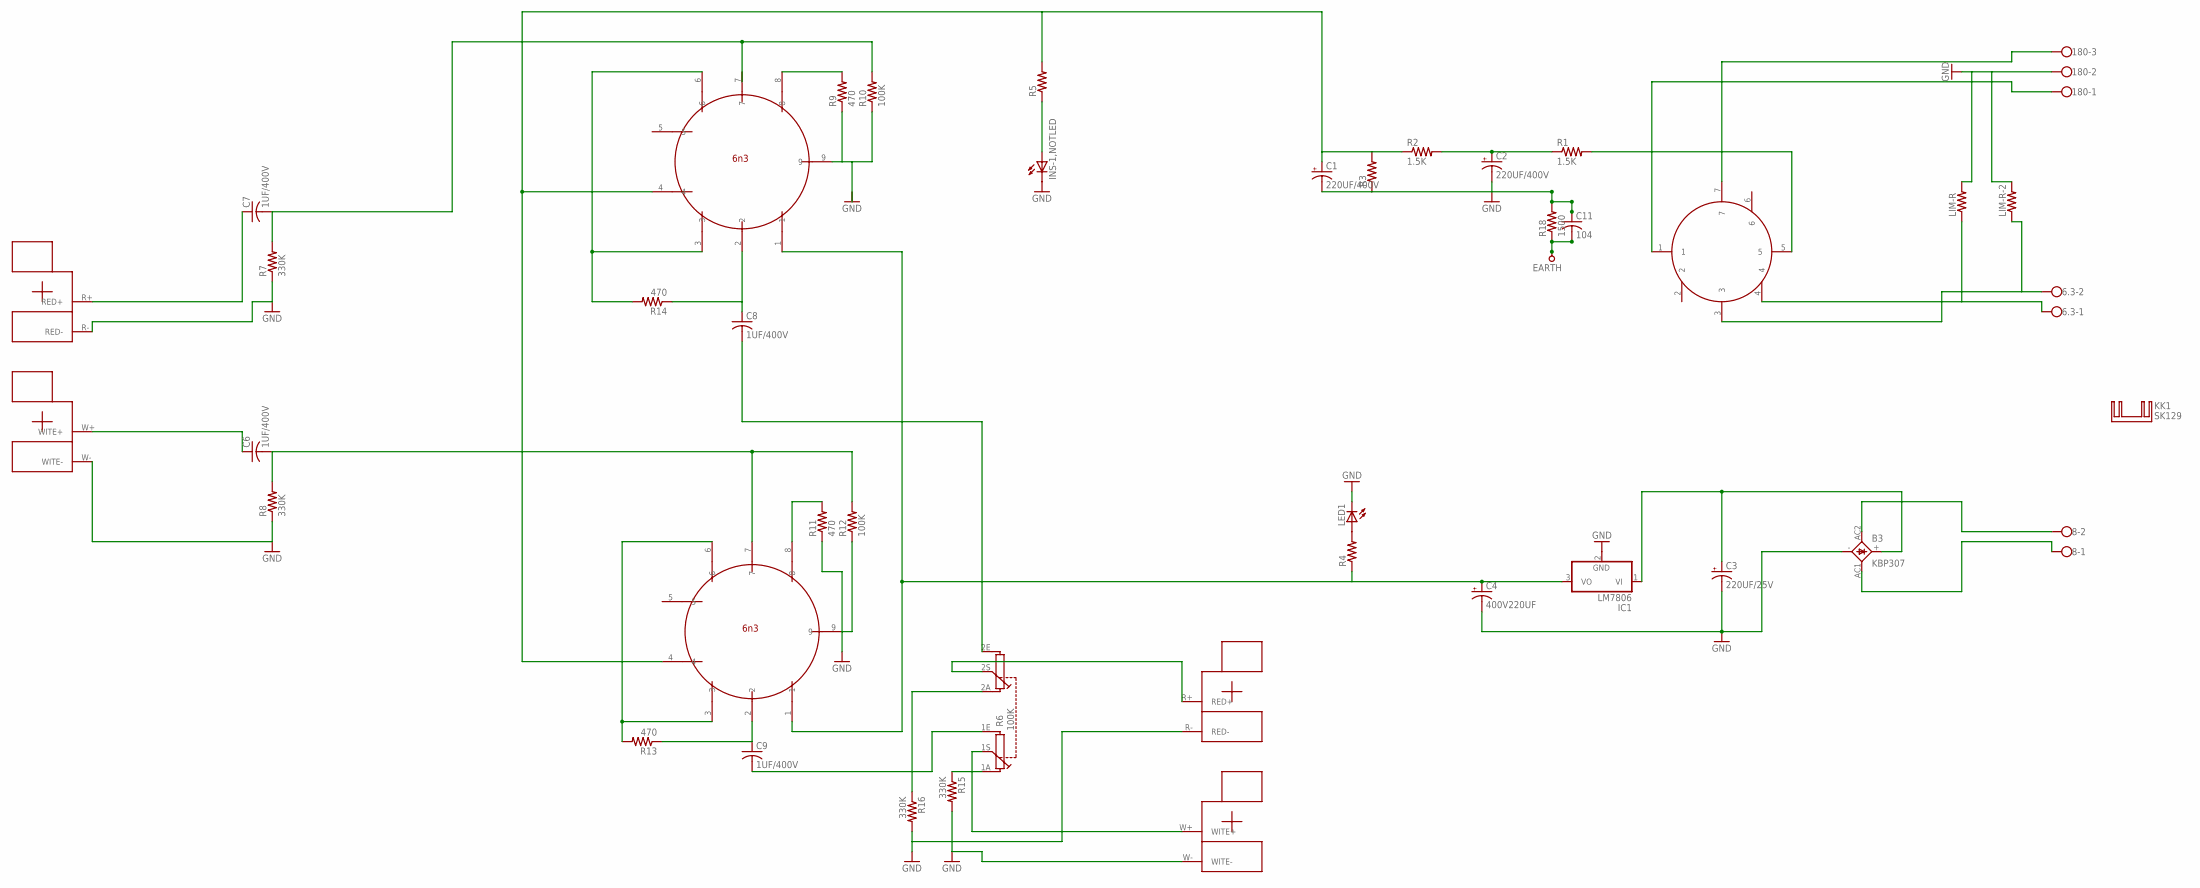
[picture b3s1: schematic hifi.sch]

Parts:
6.3, 8: W237-102
180: W237-103
B3: KBP307; KBL
C1, C2: 220UF/400V; EB35D
C3: 220UF/25V; E3,5-10
C4: 400V220UF; EB30D
C6, C7, C8, C9: 1UF/400V; C375-192X418
C11: 104; C075-052X106
EARTH: PAD_TERMINAL-4.1MMROUND; PAD_ROUND_4.1MM
IC1: LM7806; TO220V
INS-1,NOTLED: LED5MM
KK1: SK129; SK129-HOLE
LED1: LED5MM
LIM-R: R-US_0207/10; 0207/10
LIM-R-2: R-US_0207/10; 0207/10
R1, R2: 1.5K; 0309/12
R3, R5: R-US_0309/12; 0309/12
R4: R-US_0207/10; 0207/10
R6: 100K; PC16D
R7, R8, R15, R16: 330K; 0207/10
R9, R11, R13, R14: 470; 0207/10
R10, R12: 100K; 0207/10
R18: 1500; 0309/12
U$1: 6Z4-SIMPLE; MINI_P7
U$2, U$3: 6N3-SIMPLE; NOVAL
U$4, U$5: RCANEW; RCA

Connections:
GND: 180.2, B3.-, C1.-, C2.-, C3.-, C4.-, C11.1, IC1.2 (GND), INS-1,NOTLED.K (C), LED1.K (C), LIM-R.2, LIM-R-2.2, R3.1, R7.1, R8.1, R11.1, R12.1, R15.2, R16.2, R18.2, U$3.9, U$4.R- (RED-), U$4.W- (WITE-), U$5.R- (RED-), U$5.W- (WITE-)
unnamed: 180.3, U$1.7
unnamed: 8.2, B3.AC2 (AC1)
unnamed: 180.1, U$1.1
unnamed: 6.3.1, LIM-R.1, U$1.4
unnamed: 6.3.2, LIM-R-2.1, U$1.3
unnamed: 8.1, B3.AC1 (AC2)
unnamed: B3.+, C3.+, IC1.1 (VI)
unnamed: C4.+, IC1.3 (VO), R4.1, U$2.1, U$3.1
unnamed: INS-1,NOTLED.A, R5.1
unnamed: C2.+, R1.1, R2.2
unnamed: C11.2, EARTH.P, R18.1
unnamed: C6.1, U$4.W+ (WITE+)
unnamed: R1.2, U$1.5
unnamed: C1.+, R2.1, R3.2, R5.2, U$2.4, U$3.4
unnamed: C7.1, U$4.R+ (RED+)
unnamed: LED1.A, R4.2
unnamed: R6.1S, U$5.W+ (WITE+)
unnamed: C8.1, R14.1, U$2.2
unnamed: C7.2, R7.2, R10.2
unnamed: C6.2, R8.2, R12.2, U$3.7
unnamed: R14.2, U$2.3, U$2.6
unnamed: C8.2, R6.2E
unnamed: R6.2A, R16.1
unnamed: R6.1A, R15.1
unnamed: C9.2, R6.1E
unnamed: C9.1, R13.1, U$3.2
unnamed: R13.2, U$3.3, U$3.6
unnamed: R6.2S, U$5.R+ (RED+)
unnamed: R9.1, R10.1, U$2.9
unnamed: R9.2, U$2.8
unnamed: R11.2, U$3.8

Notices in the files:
parts and their libraries:
SparkFun-RF: Licensing: Creative Commons ShareAlike 4.0 International - https://creativecommons.org/licenses/by-sa/4.0
microbuilder: This work is placed in the public domain, and may be freely used for commercial and non-commercial work with the following conditions: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
